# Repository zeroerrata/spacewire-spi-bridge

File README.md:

<p align="center">
  <a href="https://zeroerrata.eu"><picture>
    <source media="(prefers-color-scheme: dark)" srcset="images/zeroerrata-logo-dark.png">
    
  </picture></a>
</p>

<h1 align="center">SpaceWire to SPI bridge with SDRAM FIFO</h1>

<p align="center"><b>A stand-alone adapter between a SpaceWire link and a host MCU on SPI, with 32 MB of SDRAM buffering in a Lattice MachXO2.</b></p>

## About

A stand-alone bridge between one SpaceWire link (ECSS-E-ST-50-12C, 100 Mbit/s, LVDS) and a host microcontroller on SPI (slave, up to 80 MHz, with an interrupt line). A Lattice MachXO2-7000HC FPGA in TQFP-144 runs the SpaceWire codec and two packet FIFOs in a 32 MB SDRAM at 100 MHz, so neither side has to keep up with the other in real time.

Revision 2 places a dedicated 100 nF decoupling capacitor on the bottom side right under every FPGA and SDRAM supply pin. 5 V comes from USB-C, one 3.3 V buck rail feeds the board; the 4-layer board has controlled impedance for the single-ended and LVDS lines.

## Features

- Lattice LCMXO2-7000HC-4TG144C (non-BGA, internal flash, single 3.3 V)
- Alliance AS4C16M16SA 32 MB SDRAM (rev 3; Winbond W9825G6KH before) at 100 MHz CL2 as packet FIFO in each direction
- SpaceWire port with a TI SN65LVDS049 LVDS PHY: micro-D 9S on flying leads or a 1 x 10 lab header
- SPI slave mode 0 up to 80 MHz with IRQ, IRQ2 and RESET on a Pmod Type 2A header
- USB-C 5 V (power only) to a TLV62569 3.3 V / 2 A buck
- Reset and PROG buttons, power and 6 status LEDs, JTAG header for the Lattice cable, debug header

## Specifications

| | |
|---|---|
| Board | 78.0 x 66.0 mm, 4 copper layers, 1.6 mm |
| Finish | ENIG |
| Parts | 102 |
| Release | rev 3, 2026-11-27 |
| SpaceWire | 1 port, 100 Mbit/s, LVDS 100 ohm |
| Host interface | SPI slave, mode 0, up to 80 MHz, IRQ |
| Buffer | 32 MB SDRAM, 16 bit, 100 MHz |
| Supply | USB-C 5 V, about 0.3 A at 3.3 V |
| Stackup | 4 layers, 1.6 mm, controlled impedance (50 ohm single-ended, 100 ohm LVDS) |

## Performance (simulated)

Predictions from the design data, not measurements.

- Controlled impedance from a field solver on the real stackup: single-ended 50.1 ohm, LVDS pair 100.0 ohm.
- Thermal: 0.73 W in total, board maximum 34.1 C at 25 C ambient, still air, horizontal board.

## Renders

| Top | Bottom | Low |
|---|---|---|
|  |  |  |

## Files

| Folder | Contents |
|---|---|
| [`kicad/`](kicad) | KiCad 10 project: schematic, board, design rules, project libraries |
| [`docs/`](docs) | [schematic.pdf](docs/schematic.pdf), [board_layers.pdf](docs/board_layers.pdf) |
| [`fabrication/`](fabrication) | Gerber and drill files (zip), bill of materials, pick-and-place |
| [`images/`](images) | renders and copper layer pictures |
| [`analysis/`](analysis) | simulation and analysis results: bringup, dfm, eye, retpath, thermal |

## Verification

- Impedance of the single-ended (50.1 ohm) and LVDS (100.0 ohm) lines from a field solver
- Thermal map: 0.73 W, board maximum 34 C at 25 C still air: see analysis/thermal
- Every result is a prediction from design data; the board has not been measured unless stated.

## How to order

1. Upload `fabrication/gerbers_drill.zip` to your PCB fab; the stackup and finish are in the specifications above.
2. For assembly, use `fabrication/bom_jlcpcb.csv` and `fabrication/cpl_jlcpcb.csv` (JLCPCB format) or the KiCad-format `bom.csv` / `pos.csv`.
3. Check part stock and the footprints against the current data sheets before you order.

## Known issues

Found by the design review of this release; boards built from these files carry them:

- Rev 3 orders the SpaceWire micro-D by the maker's correct code (Glenair MWDM2L-9S-6E5-18B); rev 1-2 BOMs carry a mixed code that cannot be ordered.
- Reflow balance: from rev 3 the small ground pads connect through thermal reliefs; use a profile with a 60-90 s soak at 150-180 C and inspect the small parts.
- SDRAM (rev 3): the Alliance part needs tRCD / tRP of at least 18 ns (2 cycles at 100 MHz) and its power-up sequence in the FPGA design; the Winbond -6 grade of earlier revisions is not recommended for new designs.

## Notes

- The renders show the ZeroErrata house look; from rev 3 the fabrication package specifies it too: matte black solder mask, white silkscreen, ENIG.
- The FPGA design (SpaceWire codec, FIFOs, SPI slave) is not part of this repository; check the pin map in Lattice Diamond before you order.

## Licence

Released under the [CERN Open Hardware Licence Version 2 - Permissive](LICENSE) (CERN-OHL-P-2.0): use, modify, make and sell it, also commercially. Provided as is, without warranty.

---

<p align="center">
  Designed by <a href="https://zeroerrata.eu"><b>ZeroErrata</b></a>: PCB design, verified before it is ordered.<br>
  <a href="https://zeroerrata.eu">zeroerrata.eu</a> · <a href="mailto:hello@zeroerrata.eu">hello@zeroerrata.eu</a>
</p>

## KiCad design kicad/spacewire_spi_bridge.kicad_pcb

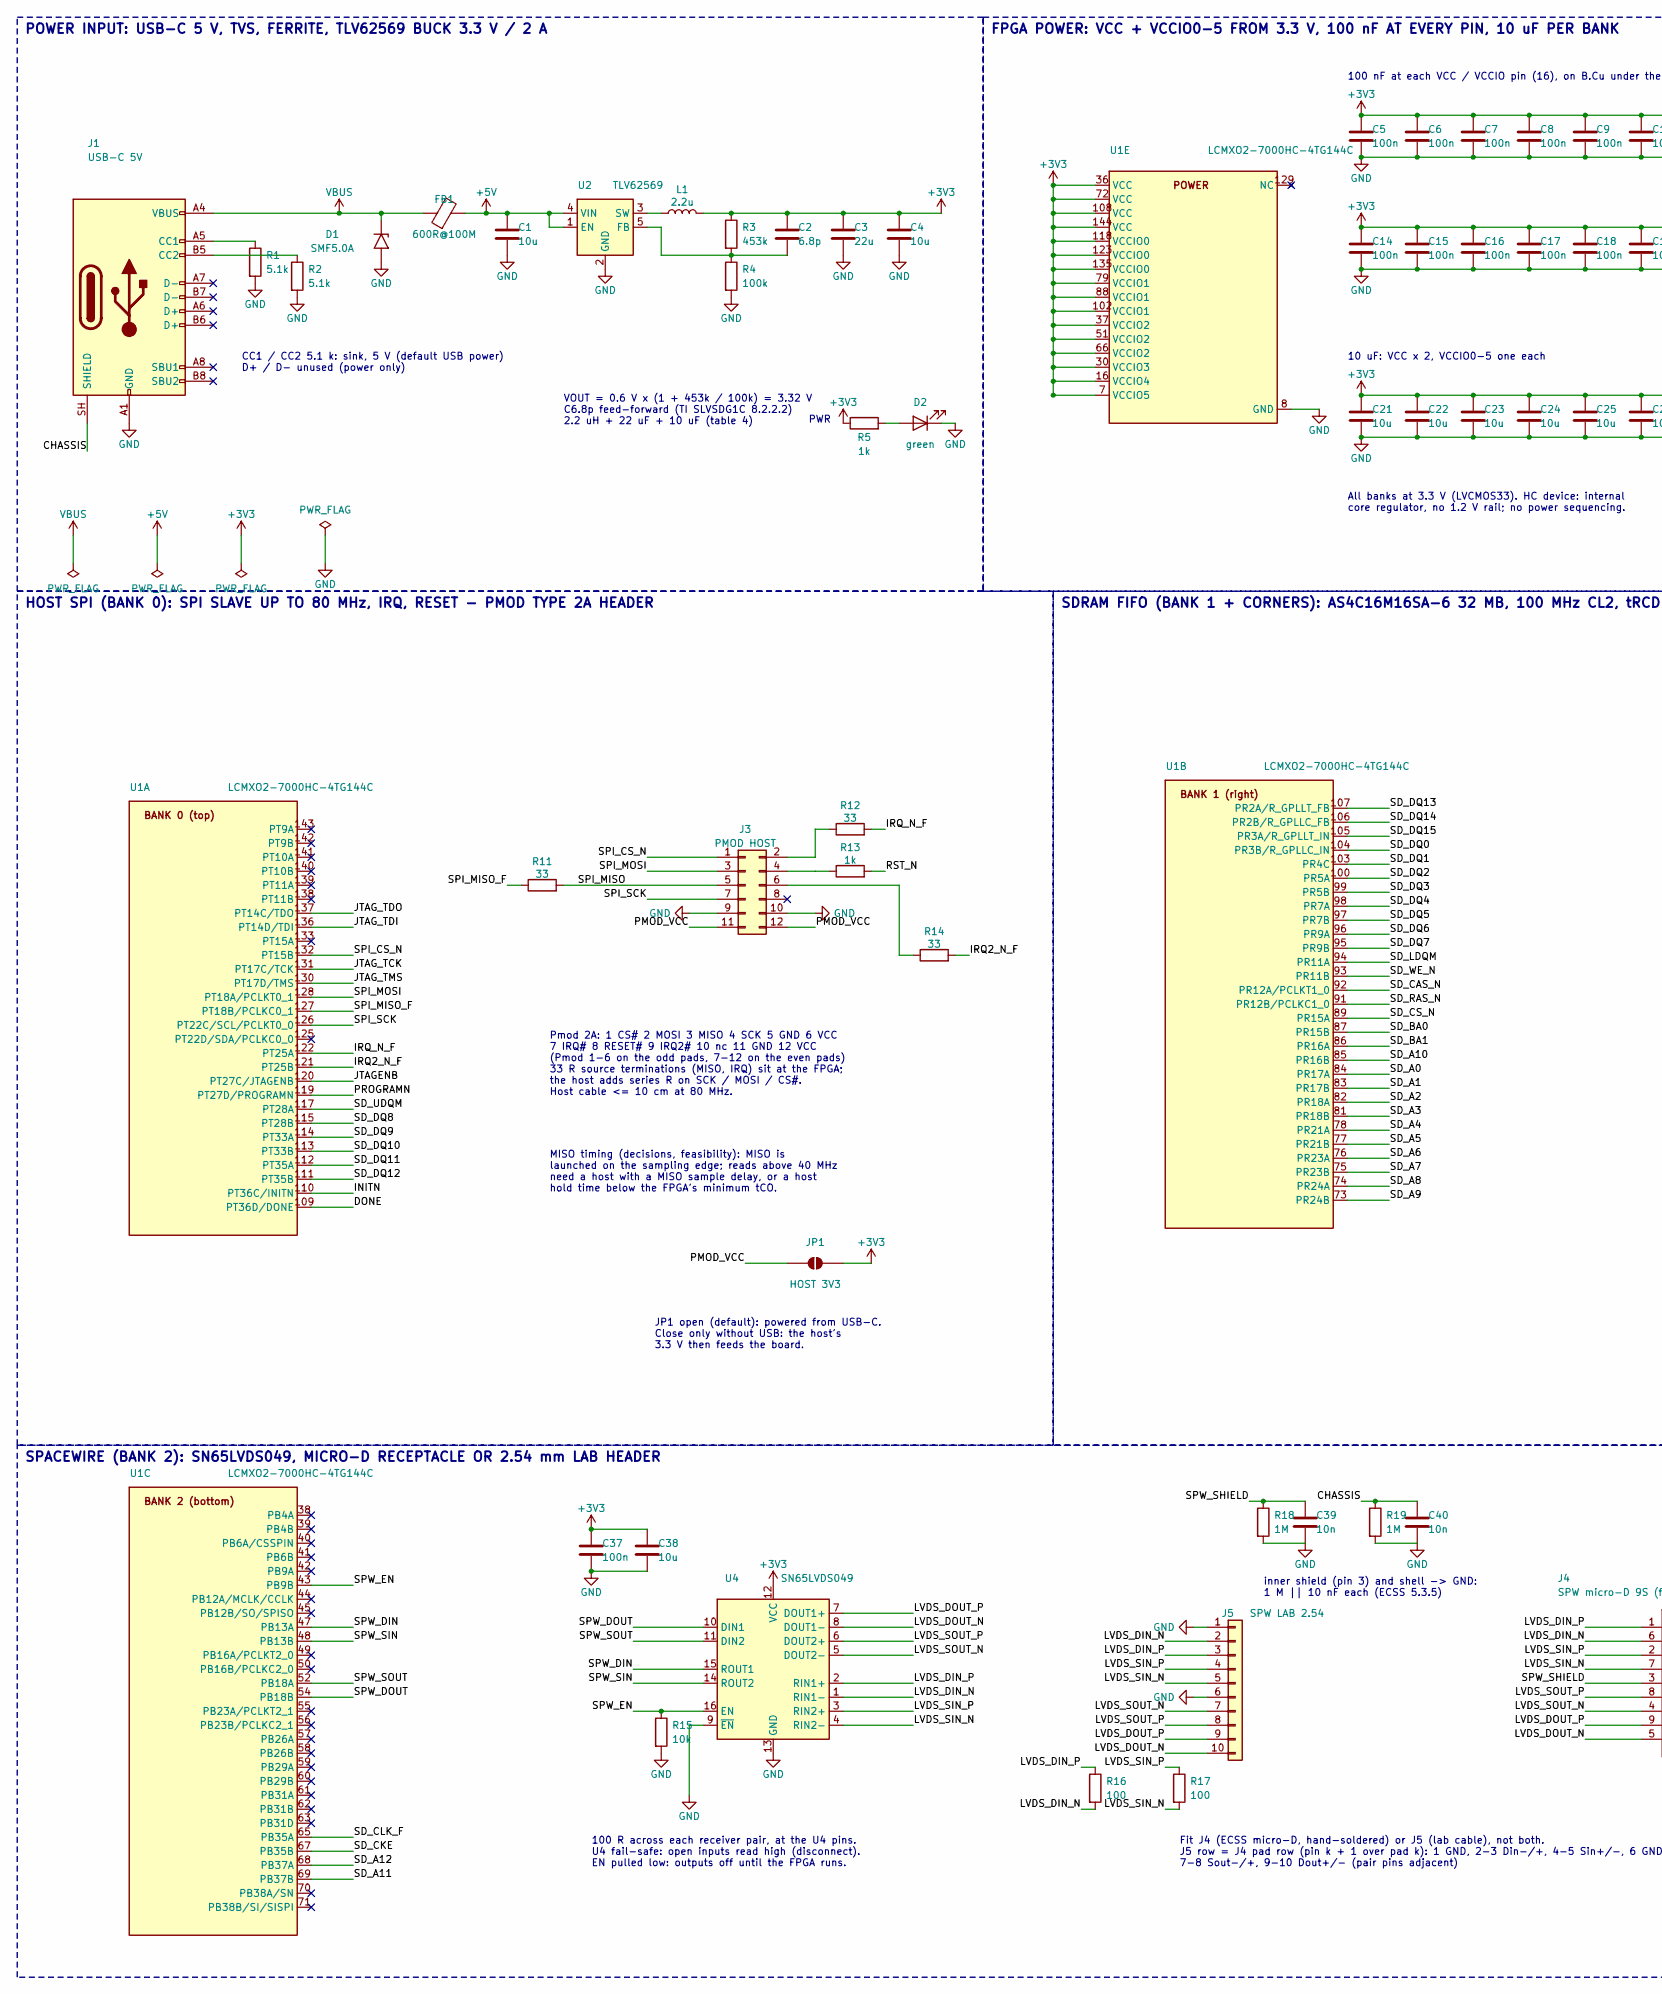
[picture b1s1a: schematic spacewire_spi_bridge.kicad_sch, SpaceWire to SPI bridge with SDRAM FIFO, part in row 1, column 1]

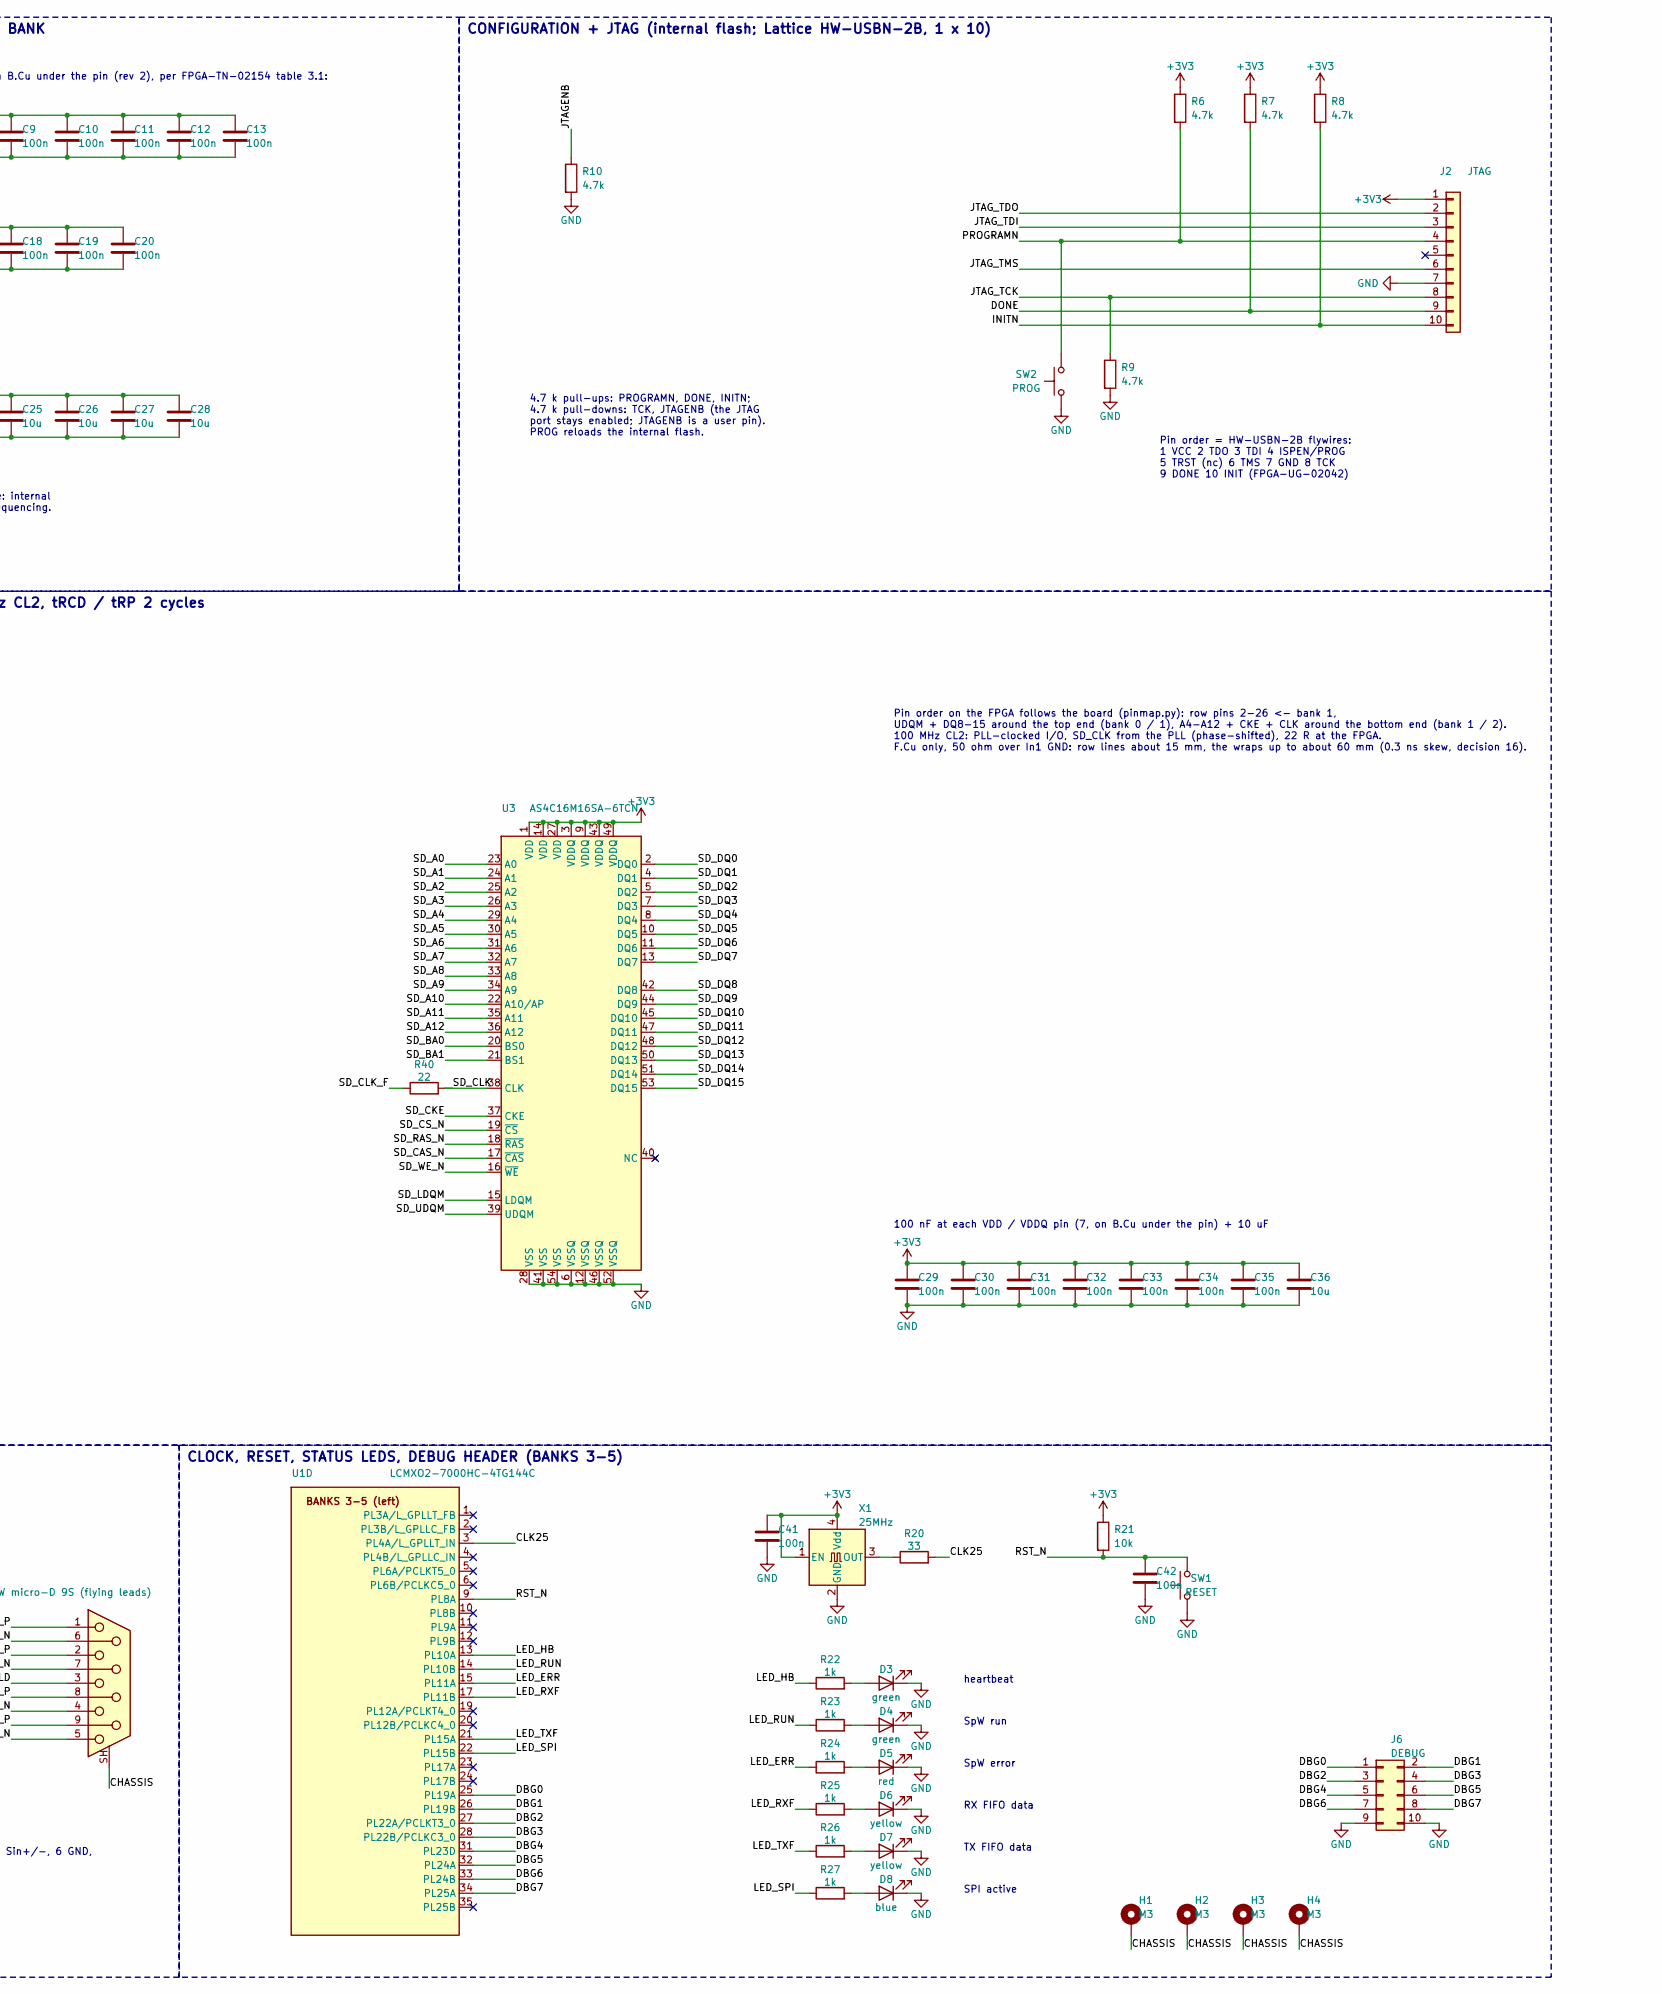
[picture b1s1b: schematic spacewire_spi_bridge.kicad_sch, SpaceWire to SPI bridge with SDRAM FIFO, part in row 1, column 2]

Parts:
C1, C4, C21, C22, C23, C24, C25, C26, C27, C28, C36, C38: 10u; C_0603_1608Metric; MPN CL10A106KP8NNNC; LCSC C19702
C2: 6.8p; C_0402_1005Metric; MPN CL05C6R8CB5NNNC; LCSC C318598
C3: 22u; C_0805_2012Metric; MPN CL21A226MAYNNNE; LCSC C602037
C5, C6, C7, C8, C9, C10, C11, C12, C13, C14, C15, C16, C17, C18, C19, C20, C29, C30, C31, C32, C33, C34, C35, C37, C41, C42: 100n; C_0402_1005Metric; MPN CL05B104KO5NNNC; LCSC C1525
C39, C40: 10n; C_0402_1005Metric; MPN CL05B103KB5NNNC; LCSC C15195
D1: SMF5.0A; D_SMF; MPN SMF5.0A; LCSC C193402
D2, D3, D4: green; LED_0603_1608Metric; MPN KT-0603G; LCSC C12624
D5: red; LED_0603_1608Metric; MPN KT-0603R; LCSC C2286
D6, D7: yellow; LED_0603_1608Metric; MPN KT-0603Y; LCSC C2287
D8: blue; LED_0603_1608Metric; MPN KT-0603B; LCSC C2288
FB1: 600R@100M; L_0603_1608Metric; MPN BLM18KG601SN1D; LCSC C85833
H1, H2, H3, H4: M3; MountingHole_3.2mm_M3_Pad_Via
J1: USB-C 5V; USB_C_Receptacle_HRO_TYPE-C-31-M-12; MPN TYPE-C-31-M-12; LCSC C165948
J2: JTAG; PinHeader_1x10_P2.54mm_Vertical; MPN PZ254V-11-10P; LCSC C492409
J3: PMOD HOST; PinHeader_2x06_P2.54mm_Horizontal_EdgeOverhang; MPN PZ254R-12-12P; LCSC C492434
J4: SPW micro-D 9S (flying leads); MicroD9_FlyingLeads; MPN MWDM2L-9S-6E5-18B
J5: SPW LAB 2.54; PinHeader_1x10_P2.54mm_Vertical; MPN PZ254V-11-10P; LCSC C492409
J6: DEBUG; PinHeader_2x05_P2.54mm_Vertical; MPN PZ254V-12-10P; LCSC C492422
JP1: HOST 3V3; SolderJumper-2_P1.3mm_Open_RoundedPad1.0x1.5mm
L1: 2.2u; L_Sunlord_SWPA4020S; MPN SWPA4020S2R2NT; LCSC C305171
R1, R2: 5.1k; R_0402_1005Metric; MPN 0402WGF5101TCE; LCSC C25905
R3: 453k; R_0402_1005Metric; MPN 0402WGF4533TCE; LCSC C27009
R4: 100k; R_0402_1005Metric; MPN 0402WGF1003TCE; LCSC C25741
R5, R13, R22, R23, R24, R25, R26, R27: 1k; R_0402_1005Metric; MPN 0402WGF1001TCE; LCSC C11702
R6, R7, R8, R9, R10: 4.7k; R_0402_1005Metric; MPN 0402WGF4701TCE; LCSC C25900
R11, R12, R14, R20: 33; R_0402_1005Metric; MPN 0402WGF330JTCE; LCSC C25105
R15, R21: 10k; R_0402_1005Metric; MPN 0402WGF1002TCE; LCSC C25744
R16, R17: 100; R_0402_1005Metric; MPN 0402WGF1000TCE; LCSC C25076
R18, R19: 1M; R_0402_1005Metric; MPN 0402WGF1004TCE; LCSC C26083
R40: 22; R_0402_1005Metric; MPN 0402WGF220JTCE; LCSC C25092
SW1: RESET; SW_Push_1P1T_XKB_TS-1187A; MPN TS-1187A-B-A-B; LCSC C318884
SW2: PROG; SW_Push_1P1T_XKB_TS-1187A; MPN TS-1187A-B-A-B; LCSC C318884
U1: LCMXO2-7000HC-4TG144C; TQFP-144_20x20mm_P0.5mm; MPN LCMXO2-7000HC-4TG144C; LCSC C7296622
U2: TLV62569; SOT-23-5; MPN TLV62569DBVR; LCSC C141836
U3: AS4C16M16SA-6TCN; TSOP-II-54_22.2x10.16mm_P0.8mm; MPN AS4C16M16SA-6TCN; LCSC C2063698
U4: SN65LVDS049; TSSOP-16_4.4x5mm_P0.65mm; MPN SN65LVDS049PW; LCSC C206168
X1: 25MHz; Oscillator_SMD_Abracon_ASE-4Pin_3.2x2.5mm; MPN OT322525MJBA4SL; LCSC C669088

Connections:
+3V3: C2.1, C3.1, C4.1, C5.1, C6.1, C7.1, C8.1, C9.1, C10.1, C11.1, C12.1, C13.1, C14.1, C15.1, C16.1, C17.1, C18.1, C19.1, C20.1, C21.1, C22.1, C23.1, C24.1, C25.1, C26.1, C27.1, C28.1, C29.1, C30.1, C31.1, C32.1, C33.1, C34.1, C35.1, C36.1, C37.1, C38.1, C41.1, J2.1, JP1.2 (B), L1.2, R3.1, R5.1, R6.1, R7.1, R8.1, R21.1, U1.7 (VCCIO5), U1.16 (VCCIO4), U1.30 (VCCIO3), U1.36 (VCC), U1.37 (VCCIO2), U1.51 (VCCIO2), U1.66 (VCCIO2), U1.72 (VCC), U1.79 (VCCIO1), U1.88 (VCCIO1), U1.102 (VCCIO1), U1.108 (VCC), U1.118 (VCCIO0), U1.123 (VCCIO0), U1.135 (VCCIO0), U1.144 (VCC), U3.1 (VDD), U3.3 (VDDQ), U3.9 (VDDQ), U3.14 (VDD), U3.27 (VDD), U3.43 (VDDQ), U3.49 (VDDQ), U4.12 (VCC), X1.1 (EN), X1.4 (Vdd)
+5V: C1.1, FB1.2, U2.1 (EN), U2.4 (VIN)
/CHASSIS: C40.1, H1.1, H2.1, H3.1, H4.1, J1.SH (SHIELD), J4.SH (PAD), R19.1
/CLK25: R20.2, U1.3 (PL4A/L_GPLLT_IN)
/DBG0: J6.1, U1.25 (PL19A)
/DBG1: J6.2, U1.26 (PL19B)
/DBG2: J6.3, U1.27 (PL22A/PCLKT3_0)
/DBG3: J6.4, U1.28 (PL22B/PCLKC3_0)
/DBG4: J6.5, U1.31 (PL23D)
/DBG5: J6.6, U1.32 (PL24A)
/DBG6: J6.7, U1.33 (PL24B)
/DBG7: J6.8, U1.34 (PL25A)
/DONE: J2.9, R7.2, U1.109 (PT36D/DONE)
/INITN: J2.10, R8.2, U1.110 (PT36C/INITN)
/IRQ2_N_F: R14.2, U1.121 (PT25B)
/IRQ_N_F: R12.2, U1.122 (PT25A)
/JTAGENB: R10.1, U1.120 (PT27C/JTAGENB)
/JTAG_TCK: J2.8, R9.1, U1.131 (PT17C/TCK)
/JTAG_TDI: J2.3, U1.136 (PT14D/TDI)
/JTAG_TDO: J2.2, U1.137 (PT14C/TDO)
/JTAG_TMS: J2.6, U1.130 (PT17D/TMS)
/LED_ERR: R24.1, U1.15 (PL11A)
/LED_HB: R22.1, U1.13 (PL10A)
/LED_RUN: R23.1, U1.14 (PL10B)
/LED_RXF: R25.1, U1.17 (PL11B)
/LED_SPI: R27.1, U1.22 (PL15B)
/LED_TXF: R26.1, U1.21 (PL15A)
/LVDS_DIN_N: J4.6, J5.2, R16.2, U4.1 (RIN1-)
/LVDS_DIN_P: J4.1, J5.3, R16.1, U4.2 (RIN1+)
/LVDS_DOUT_N: J4.5, J5.10, U4.8 (DOUT1-)
/LVDS_DOUT_P: J4.9, J5.9, U4.7 (DOUT1+)
/LVDS_SIN_N: J4.7, J5.5, R17.2, U4.4 (RIN2-)
/LVDS_SIN_P: J4.2, J5.4, R17.1, U4.3 (RIN2+)
/LVDS_SOUT_N: J4.4, J5.7, U4.5 (DOUT2-)
/LVDS_SOUT_P: J4.8, J5.8, U4.6 (DOUT2+)
/PMOD_VCC: J3.11, J3.12, JP1.1 (A)
/PROGRAMN: J2.4, R6.2, SW2.2, U1.119 (PT27D/PROGRAMN)
/RST_N: C42.1, R13.2, R21.2, SW1.2, U1.9 (PL8A)
/SD_A0: U1.84 (PR17A), U3.23 (A0)
/SD_A1: U1.83 (PR17B), U3.24 (A1)
/SD_A2: U1.82 (PR18A), U3.25 (A2)
/SD_A3: U1.81 (PR18B), U3.26 (A3)
/SD_A4: U1.78 (PR21A), U3.29 (A4)
/SD_A5: U1.77 (PR21B), U3.30 (A5)
/SD_A6: U1.76 (PR23A), U3.31 (A6)
/SD_A7: U1.75 (PR23B), U3.32 (A7)
/SD_A8: U1.74 (PR24A), U3.33 (A8)
/SD_A9: U1.73 (PR24B), U3.34 (A9)
/SD_A10: U1.85 (PR16B), U3.22 (A10/AP)
/SD_A11: U1.69 (PB37B), U3.35 (A11)
/SD_A12: U1.68 (PB37A), U3.36 (A12)
/SD_BA0: U1.87 (PR15B), U3.20 (BS0)
/SD_BA1: U1.86 (PR16A), U3.21 (BS1)
/SD_CAS_N: U1.92 (PR12A/PCLKT1_0), U3.17 (~CAS)
/SD_CKE: U1.67 (PB35B), U3.37 (CKE)
/SD_CLK: R40.2, U3.38 (CLK)
/SD_CLK_F: R40.1, U1.65 (PB35A)
/SD_CS_N: U1.89 (PR15A), U3.19 (~CS)
/SD_DQ0: U1.104 (PR3B/R_GPLLC_IN), U3.2 (DQ0)
/SD_DQ1: U1.103 (PR4C), U3.4 (DQ1)
/SD_DQ2: U1.100 (PR5A), U3.5 (DQ2)
/SD_DQ3: U1.99 (PR5B), U3.7 (DQ3)
/SD_DQ4: U1.98 (PR7A), U3.8 (DQ4)
/SD_DQ5: U1.97 (PR7B), U3.10 (DQ5)
/SD_DQ6: U1.96 (PR9A), U3.11 (DQ6)
/SD_DQ7: U1.95 (PR9B), U3.13 (DQ7)
/SD_DQ8: U1.115 (PT28B), U3.42 (DQ8)
/SD_DQ9: U1.114 (PT33A), U3.44 (DQ9)
/SD_DQ10: U1.113 (PT33B), U3.45 (DQ10)
/SD_DQ11: U1.112 (PT35A), U3.47 (DQ11)
/SD_DQ12: U1.111 (PT35B), U3.48 (DQ12)
/SD_DQ13: U1.107 (PR2A/R_GPLLT_FB), U3.50 (DQ13)
/SD_DQ14: U1.106 (PR2B/R_GPLLC_FB), U3.51 (DQ14)
/SD_DQ15: U1.105 (PR3A/R_GPLLT_IN), U3.53 (DQ15)
/SD_LDQM: U1.94 (PR11A), U3.15 (LDQM)
/SD_RAS_N: U1.91 (PR12B/PCLKC1_0), U3.18 (~RAS)
/SD_UDQM: U1.117 (PT28A), U3.39 (UDQM)
/SD_WE_N: U1.93 (PR11B), U3.16 (~WE)
/SPI_CS_N: J3.1, U1.132 (PT15B)
/SPI_MISO: J3.5, R11.2
/SPI_MISO_F: R11.1, U1.127 (PT18B/PCLKC0_1)
/SPI_MOSI: J3.3, U1.128 (PT18A/PCLKT0_1)
/SPI_SCK: J3.7, U1.126 (PT22C/SCL/PCLKT0_0)
/SPW_DIN: U1.47 (PB13A), U4.15 (ROUT1)
/SPW_DOUT: U1.54 (PB18B), U4.10 (DIN1)
/SPW_EN: R15.1, U1.43 (PB9B), U4.16 (EN)
/SPW_SHIELD: C39.1, J4.3, R18.1
/SPW_SIN: U1.48 (PB13B), U4.14 (ROUT2)
/SPW_SOUT: U1.52 (PB18A), U4.11 (DIN2)
GND: C1.2, C3.2, C4.2, C5.2, C6.2, C7.2, C8.2, C9.2, C10.2, C11.2, C12.2, C13.2, C14.2, C15.2, C16.2, C17.2, C18.2, C19.2, C20.2, C21.2, C22.2, C23.2, C24.2, C25.2, C26.2, C27.2, C28.2, C29.2, C30.2, C31.2, C32.2, C33.2, C34.2, C35.2, C36.2, C37.2, C38.2, C39.2, C40.2, C41.2, C42.2, D1.2 (A2), D2.1 (K), D3.1 (K), D4.1 (K), D5.1 (K), D6.1 (K), D7.1 (K), D8.1 (K), J1.A1 (GND), J1.A12 (GND), J1.B1 (GND), J1.B12 (GND), J2.7, J3.9, J3.10, J5.1, J5.6, J6.9, J6.10, R1.2, R2.2, R4.2, R9.2, R10.2, R15.2, R18.2, R19.2, SW1.1, SW2.1, U1.8 (GND), U1.18 (GND), U1.29 (GND), U1.46 (GND), U1.53 (GND), U1.64 (GND), U1.80 (GND), U1.90 (GND), U1.101 (GND), U1.116 (GND), U1.124 (GND), U1.134 (GND), U2.2 (GND), U3.6 (VSSQ), U3.12 (VSSQ), U3.28 (VSS), U3.41 (VSS), U3.46 (VSSQ), U3.52 (VSSQ), U3.54 (VSS), U4.9 (~EN), U4.13 (GND), X1.2 (GND)
unnamed: D2.2 (A), R5.2
unnamed: D3.2 (A), R22.2
unnamed: D4.2 (A), R23.2
unnamed: D5.2 (A), R24.2
unnamed: D6.2 (A), R25.2
unnamed: D7.2 (A), R26.2
unnamed: D8.2 (A), R27.2
unnamed: J1.A5 (CC1), R1.1
unnamed: J1.B5 (CC2), R2.1
unnamed: J3.2, R12.1
unnamed: J3.4, R13.1
unnamed: J3.6, R14.1
unnamed: C2.2, R3.2, R4.1, U2.5 (FB)
unnamed: L1.1, U2.3 (SW)
unnamed: R20.1, X1.3 (OUT)
VBUS: D1.1 (A1), FB1.1, J1.A4 (VBUS), J1.A9 (VBUS), J1.B4 (VBUS), J1.B9 (VBUS)

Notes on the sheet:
POWER INPUT: USB-C 5 V, TVS, FERRITE, TLV62569 BUCK 3.3 V / 2 A
CC1 / CC2 5.1 k: sink, 5 V (default USB power) D+ / D- unused (power only)
VOUT = 0.6 V x (1 + 453k / 100k) = 3.32 V C6.8p feed-forward (TI SLVSDG1C 8.2.2.2) 2.2 uH + 22 uF + 10 uF (table 4)
PWR
FPGA POWER: VCC + VCCIO0-5 FROM 3.3 V, 100 nF AT EVERY PIN, 10 uF PER BANK
100 nF at each VCC / VCCIO pin (16), on B.Cu under the pin (rev 2), per FPGA-TN-02154 table 3.1:
10 uF: VCC x 2, VCCIO0-5 one each
All banks at 3.3 V (LVCMOS33). HC device: internal core regulator, no 1.2 V rail; no power sequencing.
CONFIGURATION + JTAG (internal flash; Lattice HW-USBN-2B, 1 x 10)
Pin order = HW-USBN-2B flywires: 1 VCC 2 TDO 3 TDI 4 ISPEN/PROG 5 TRST (nc) 6 TMS 7 GND 8 TCK 9 DONE 10 INIT (FPGA-UG-02042)
4.7 k pull-ups: PROGRAMN, DONE, INITN; 4.7 k pull-downs: TCK, JTAGENB (the JTAG port stays enabled; JTAGENB is a user pin). PROG reloads the internal flash.
HOST SPI (BANK 0): SPI SLAVE UP TO 80 MHz, IRQ, RESET - PMOD TYPE 2A HEADER
Pmod 2A: 1 CS# 2 MOSI 3 MISO 4 SCK 5 GND 6 VCC 7 IRQ# 8 RESET# 9 IRQ2# 10 nc 11 GND 12 VCC (Pmod 1-6 on the odd pads, 7-12 on the even pads) 33 R source terminations (MISO, IRQ) sit at the FPGA; the host adds series R on SCK / MOSI / CS#. Host cable <= 10 cm at 80 MHz.
MISO timing (decisions, feasibility): MISO is launched on the sampling edge; reads above 40 MHz need a host with a MISO sample delay, or a host hold time below the FPGA's minimum tCO.
JP1 open (default): powered from USB-C. Close only without USB: the host's 3.3 V then feeds the board.
SDRAM FIFO (BANK 1 + CORNERS): AS4C16M16SA-6 32 MB, 100 MHz CL2, tRCD / tRP 2 cycles
100 nF at each VDD / VDDQ pin (7, on B.Cu under the pin) + 10 uF
Pin order on the FPGA follows the board (pinmap.py): row pins 2-26 <- bank 1, UDQM + DQ8-15 around the top end (bank 0 / 1), A4-A12 + CKE + CLK around the bottom end (bank 1 / 2). 100 MHz CL2: PLL-clocked I/O, SD_CLK from the PLL (phase-shifted), 22 R at the FPGA. F.Cu only, 50 ohm over In1 GND: ro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
SPACEWIRE (BANK 2): SN65LVDS049, MICRO-D RECEPTACLE OR 2.54 mm LAB HEADER
100 R across each receiver pair, at the U4 pins. U4 fail-safe: open inputs read high (disconnect). EN pulled low: outputs off until the FPGA runs.
Fit J4 (ECSS micro-D, hand-soldered) or J5 (lab cable), not both. J5 row = J4 pad row (pin k + 1 over pad k): 1 GND, 2-3 Din-/+, 4-5 Sin+/-, 6 GND, 7-8 Sout-/+, 9-10 Dout+/- (pair pins adjacent)
inner shield (pin 3) and shell -> GND: 1 M || 10 nF each (ECSS 5.3.5)
CLOCK, RESET, STATUS LEDS, DEBUG HEADER (BANKS 3-5)
heartbeat
SpW run
SpW error
RX FIFO data
TX FIFO data
SPI active

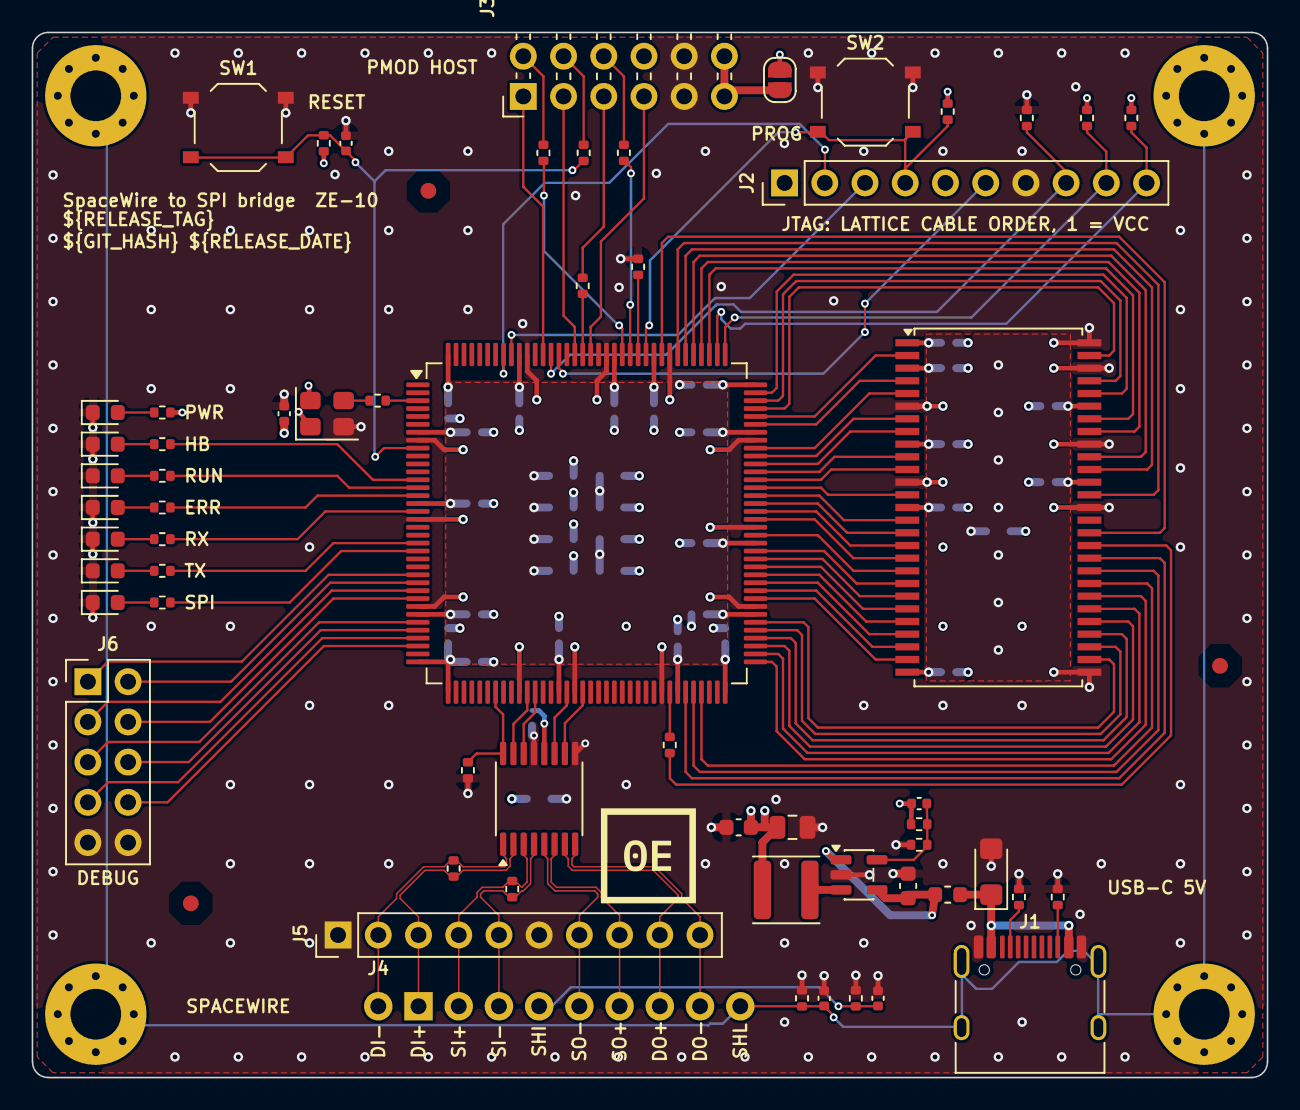
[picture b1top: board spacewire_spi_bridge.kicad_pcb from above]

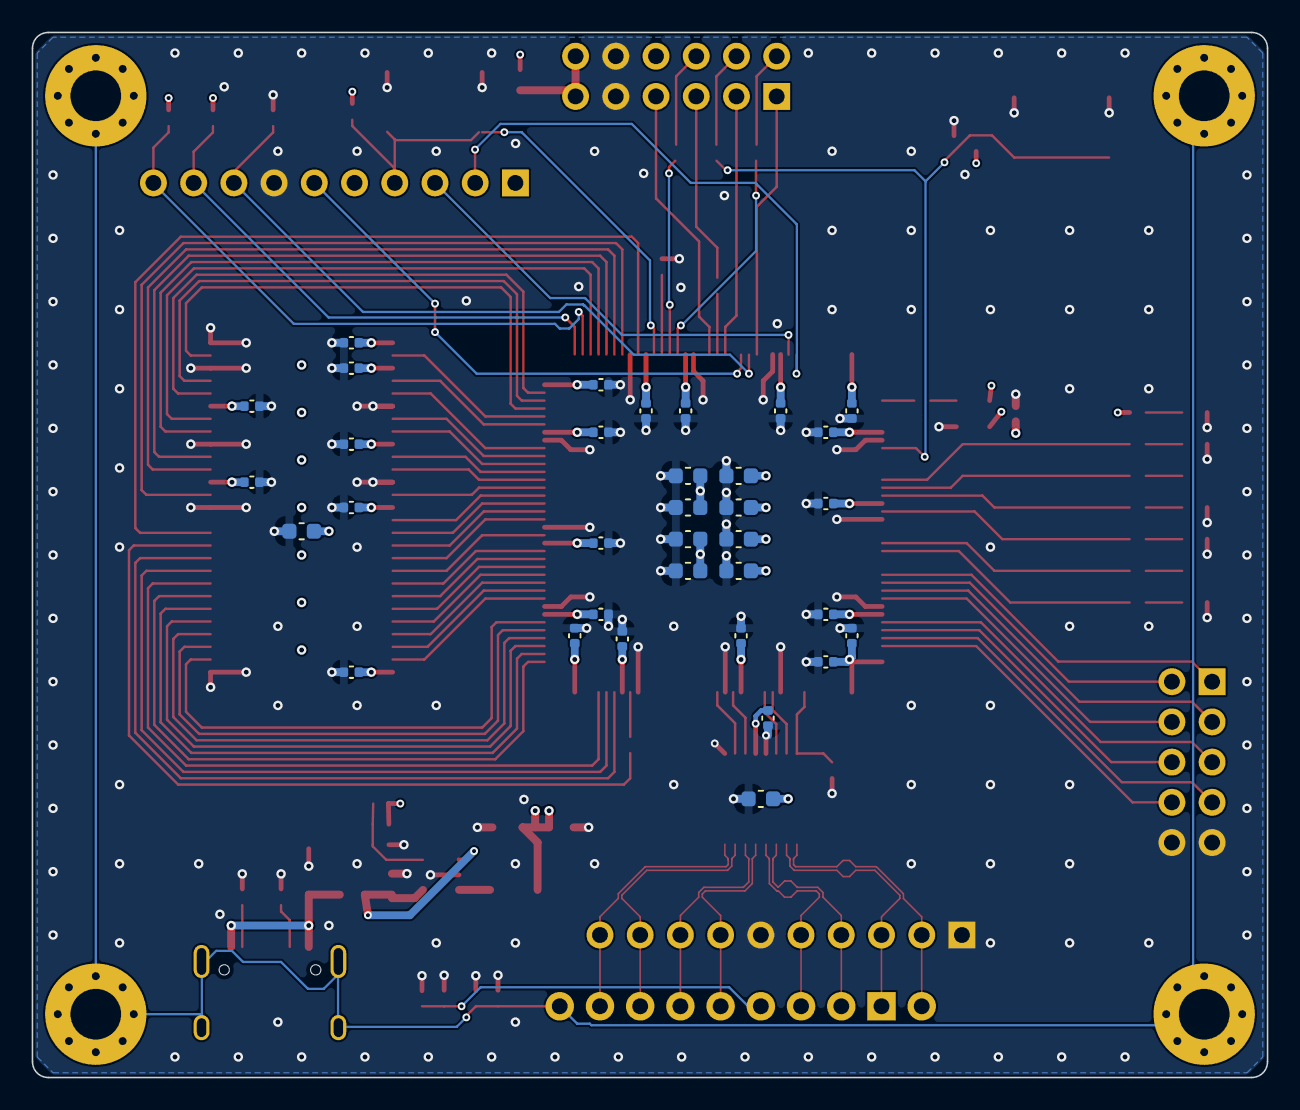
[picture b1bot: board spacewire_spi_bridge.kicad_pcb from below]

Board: 4 copper layers, 78.0 x 66.0 mm, 102 parts (34 on the bottom side), 106 nets.

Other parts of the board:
FID1, FID2, FID3: Fiducial_1mm_Mask2mm
LOGO1: ZeroErrata logo; ZeroErrata_mark_6mm

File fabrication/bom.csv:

"Designator","Value","Footprint","Quantity","Manufacturer","MPN","LCSC Part #"
"C1,C4,C21-C28,C36,C38","10u","Capacitor_SMD:C_0603_1608Metric","12","Samsung","CL10A106KP8NNNC","C19702"
"C2","6.8p","Capacitor_SMD:C_0402_1005Metric","1","Samsung","CL05C6R8CB5NNNC","C318598"
"C3","22u","Capacitor_SMD:C_0805_2012Metric","1","Samsung","CL21A226MAYNNNE","C602037"
"C5-C20,C29-C35,C37,C41,C42","100n","Capacitor_SMD:C_0402_1005Metric","26","Samsung","CL05B104KO5NNNC","C1525"
"C39,C40","10n","Capacitor_SMD:C_0402_1005Metric","2","Samsung","CL05B103KB5NNNC","C15195"
"D1","SMF5.0A","Diode_SMD:D_SMF","1","Littelfuse","SMF5.0A","C193402"
"D2-D4","green","LED_SMD:LED_0603_1608Metric","3","KENTO","KT-0603G","C12624"
"D5","red","LED_SMD:LED_0603_1608Metric","1","KENTO","KT-0603R","C2286"
"D6,D7","yellow","LED_SMD:LED_0603_1608Metric","2","KENTO","KT-0603Y","C2287"
"D8","blue","LED_SMD:LED_0603_1608Metric","1","KENTO","KT-0603B","C2288"
"FB1","600R@100M","Inductor_SMD:L_0603_1608Metric","1","Murata","BLM18KG601SN1D","C85833"
"J1","USB-C 5V","Connector_USB:USB_C_Receptacle_HRO_TYPE-C-31-M-12","1","HRO","TYPE-C-31-M-12","C165948"
"J2","JTAG","Connector_PinHeader_2.54mm:PinHeader_1x10_P2.54mm_Vertical","1","XFCN","PZ254V-11-10P","C492409"
"J3","PMOD HOST","spwspi:PinHeader_2x06_P2.54mm_Horizontal_EdgeOverhang","1","XFCN","PZ254R-12-12P","C492434"
"J4","SPW micro-D 9S (flying leads)","spwspi:MicroD9_FlyingLeads","1","Glenair","MWDM2L-9S-6E5-18B",""
"J5","SPW LAB 2.54","Connector_PinHeader_2.54mm:PinHeader_1x10_P2.54mm_Vertical","1","XFCN","PZ254V-11-10P","C492409"
"J6","DEBUG","Connector_PinHeader_2.54mm:PinHeader_2x05_P2.54mm_Vertical","1","XFCN","PZ254V-12-10P","C492422"
"L1","2.2u","Inductor_SMD:L_Sunlord_SWPA4020S","1","Sunlord","SWPA4020S2R2NT","C305171"
"R1,R2","5.1k","Resistor_SMD:R_0402_1005Metric","2","UNI-ROYAL","0402WGF5101TCE","C25905"
"R3","453k","Resistor_SMD:R_0402_1005Metric","1","UNI-ROYAL","0402WGF4533TCE","C27009"
"R4","100k","Resistor_SMD:R_0402_1005Metric","1","UNI-ROYAL","0402WGF1003TCE","C25741"
"R5,R13,R22-R27","1k","Resistor_SMD:R_0402_1005Metric","8","UNI-ROYAL","0402WGF1001TCE","C11702"
"R6-R10","4.7k","Resistor_SMD:R_0402_1005Metric","5","UNI-ROYAL","0402WGF4701TCE","C25900"
"R11,R12,R14,R20","33","Resistor_SMD:R_0402_1005Metric","4","UNI-ROYAL","0402WGF330JTCE","C25105"
"R15,R21","10k","Resistor_SMD:R_0402_1005Metric","2","UNI-ROYAL","0402WGF1002TCE","C25744"
"R16,R17","100","Resistor_SMD:R_0402_1005Metric","2","UNI-ROYAL","0402WGF1000TCE","C25076"
"R18,R19","1M","Resistor_SMD:R_0402_1005Metric","2","UNI-ROYAL","0402WGF1004TCE","C26083"
"R40","22","Resistor_SMD:R_0402_1005Metric","1","UNI-ROYAL","0402WGF220JTCE","C25092"
"SW1","RESET","Button_Switch_SMD:SW_Push_1P1T_XKB_TS-1187A","1","XKB","TS-1187A-B-A-B","C318884"
"SW2","PROG","Button_Switch_SMD:SW_Push_1P1T_XKB_TS-1187A","1","XKB","TS-1187A-B-A-B","C318884"
"U1","LCMXO2-7000HC-4TG144C","Package_QFP:TQFP-144_20x20mm_P0.5mm","1","Lattice","LCMXO2-7000HC-4TG144C","C7296622"
"U2","TLV62569","Package_TO_SOT_SMD:SOT-23-5","1","Texas Instruments","TLV62569DBVR","C141836"
"U3","AS4C16M16SA-6TCN","Package_SO:TSOP-II-54_22.2x10.16mm_P0.8mm","1","Alliance Memory","AS4C16M16SA-6TCN","C2063698"
"U4","SN65LVDS049","Package_SO:TSSOP-16_4.4x5mm_P0.65mm","1","Texas Instruments","SN65LVDS049PW","C206168"
"X1","25MHz","Oscillator:Oscillator_SMD_Abracon_ASE-4Pin_3.2x2.5mm","1","YXC","OT322525MJBA4SL","C669088"

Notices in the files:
parts and their libraries:
LICENSE: CERN-OHL-S-2.0
